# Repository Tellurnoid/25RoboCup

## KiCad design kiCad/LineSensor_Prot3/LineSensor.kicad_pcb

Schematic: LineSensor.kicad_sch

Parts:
A1: Arduino_Nano_v2.x; Arduino_Nano
C2: C; CP_Radial_D5.0mm_P2.50mm
C3: C; C_Disc_D7.5mm_W2.5mm_P5.00mm
C4, C5, C6, C7, C8, C9, C10, C11: C; C_0603_1608Metric
D34, D35, D36, D37, D38, D39, D40, D41, D42, D43, D44, D45, D46, D47, D48, D49: LED; LED_0603_1608Metric
J1: Conn_01x04_Socket; PinSocket_1x04_P2.54mm_Vertical
J2: Conn_01x02_Socket; PinSocket_1x02_P2.54mm_Vertical
Q1, Q2, Q3, Q4, Q5, Q6, Q7, Q8, Q9, Q10, Q11, Q12, Q13, Q14, Q15, Q16: Q_Photo_NPN; NJL7502R
Q17: NMOS; TO-251-3-1EP_Horizontal_TabDown
R1, R2, R3, R4, R5, R6, R7, R8, R9, R10, R11, R12, R13, R14, R15, R16, R17, R18, R19, R20, R21, R22, R23, R24, R25, R26, R27, R28, R29, R30, R31, R32, R33, R34, R35, R36, R37, R38, R39, R40, R41, R42, R43, R44, R45, R46, R55, R56: R; R_0603_1608Metric_Pad0.98x0.95mm_HandSolder
R49, R50, R51, R84, R85: R; R_Axial_DIN0207_L6.3mm_D2.5mm_P7.62mm_Horizontal
RV1, RV2, RV3, RV4: R_Potentiometer_Trim; PinHeader_1x03_P2.54mm_Vertical
SW2: SW_DPST_x2; PinSocket_1x03_P2.54mm_Vertical
U1, U2, U3, U4, U5, U6, U7, U8, U9: LM393; SOIC-8_3.9x4.9mm_P1.27mm

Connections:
unnamed: A1.19 (A0), R25.2, U8.7
unnamed: A1.20 (A1), R26.2, U8.1
unnamed: A1.21 (A2), R27.2, U7.7
unnamed: A1.22 (A3), R28.2, U7.1
unnamed: A1.23 (A4), R32.2, U2.7
unnamed: A1.2 (D0/RX), J1.2
unnamed: A1.1 (D1/TX), R49.2
unnamed: A1.5 (D2), R21.2, U6.7
unnamed: A1.6 (D3), R22.2, U6.1
unnamed: A1.7 (D4), R23.2, U5.7
unnamed: A1.8 (D5), R24.2, U5.1
unnamed: A1.9 (D6), R8.2, U3.1
unnamed: A1.10 (D7), R7.2, U3.7
unnamed: A1.11 (D8), R6.2, U4.1
unnamed: A1.12 (D9), R5.2, U4.7
unnamed: A1.13 (D10), R84.1
unnamed: A1.14 (D11), R29.2, U1.1, U9.1
unnamed: A1.15 (D12), R30.2, U1.7, U9.7
unnamed: A1.16 (D13), R31.2, U2.1
unnamed: D34.1 (K), R55.1
unnamed: D35.1 (K), R56.1
unnamed: D36.1 (K), R40.1
unnamed: D37.1 (K), R41.1
unnamed: D38.1 (K), R42.1
unnamed: D39.1 (K), R43.1
unnamed: D40.1 (K), R44.1
unnamed: D41.1 (K), R45.1
unnamed: D42.1 (K), R46.1
unnamed: D43.1 (K), R39.1
unnamed: D44.1 (K), R38.1
unnamed: D45.1 (K), R37.1
unnamed: D46.1 (K), R36.1
unnamed: D47.1 (K), R35.1
unnamed: D48.1 (K), R34.1
unnamed: D49.1 (K), R33.1
unnamed: J1.1, R49.1, R51.1
unnamed: J2.1, SW2.2 (B)
unnamed: Q1.2 (E), R4.1, U3.2 (-)
unnamed: Q2.2 (E), R3.1, U3.6 (-)
unnamed: Q3.2 (E), R2.1, U4.2 (-)
unnamed: Q4.2 (E), R1.1, U4.6 (-)
unnamed: Q5.2 (E), R13.1, U7.2 (-)
unnamed: Q6.2 (E), R14.1, U7.6 (-)
unnamed: Q7.2 (E), R15.1, U8.2 (-)
unnamed: Q8.2 (E), R16.1, U8.6 (-)
unnamed: Q9.2 (E), R9.1, U6.6 (-)
unnamed: Q10.2 (E), R10.1, U6.2 (-)
unnamed: Q11.2 (E), R11.1, U5.6 (-)
unnamed: Q12.2 (E), R12.1, U5.2 (-)
unnamed: Q13.2 (E), R17.1, U1.2 (-), U9.3 (+)
unnamed: Q14.2 (E), R18.1, U1.6 (-), U9.5 (+)
unnamed: Q15.2 (E), R19.1, U2.2 (-)
unnamed: Q16.2 (E), R20.1, U2.6 (-)
unnamed: Q17.1 (D), R33.2, R34.2, R35.2, R36.2, R37.2, R38.2, R39.2, R40.2, R41.2, R42.2, R43.2, R44.2, R45.2, R46.2, R55.2, R56.2
unnamed: Q17.2 (G), R84.2, R85.2
unnamed: R50.1, R51.2
unnamed: RV4.2, U1.3 (+), U1.5 (+), U2.3 (+), U2.5 (+), U9.2 (-), U9.6 (-)
unnamed: RV1.2, U3.3 (+), U3.5 (+), U4.3 (+), U4.5 (+)
unnamed: RV2.2, U5.3 (+), U5.5 (+), U6.3 (+), U6.5 (+)
unnamed: RV3.2, U7.3 (+), U7.5 (+), U8.3 (+), U8.5 (+)

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
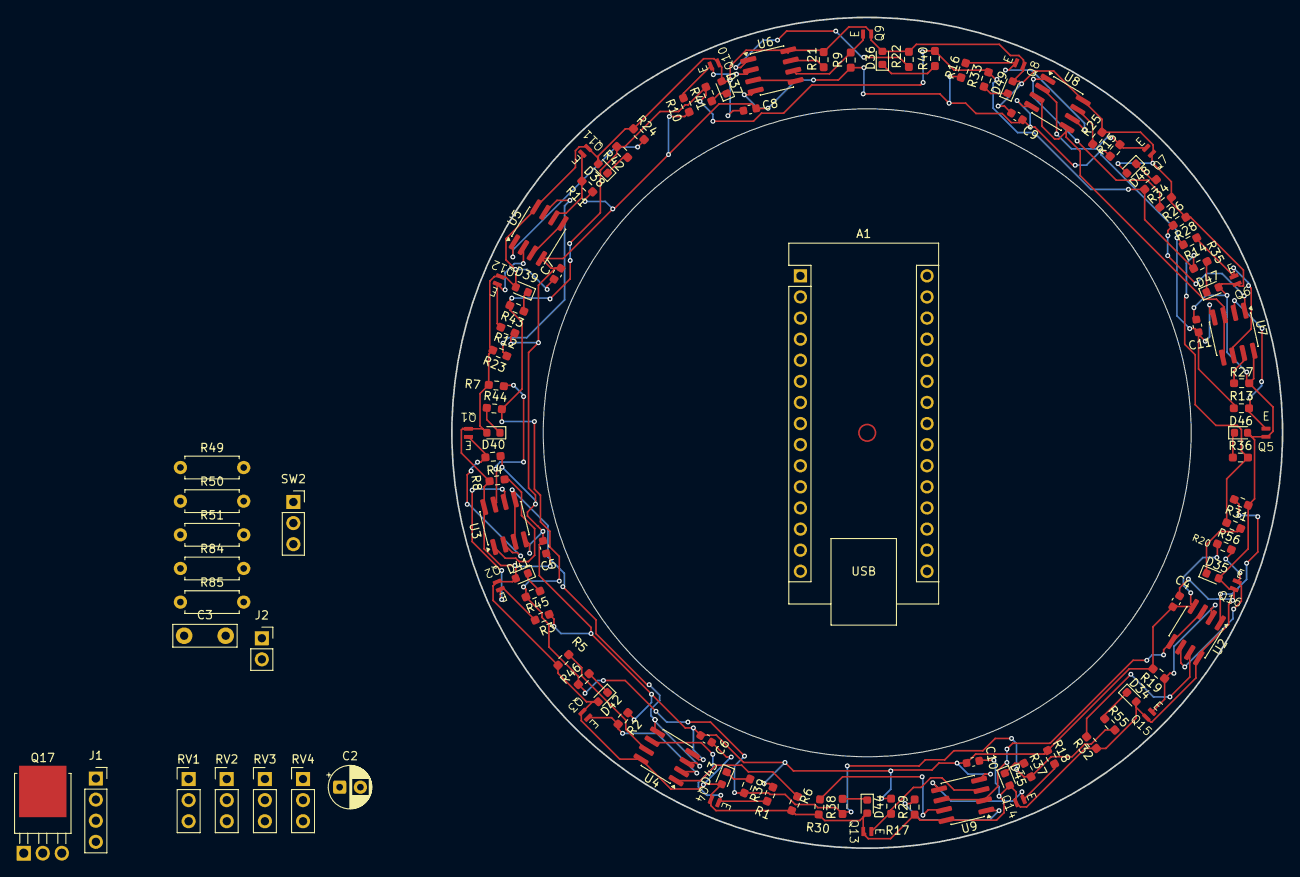
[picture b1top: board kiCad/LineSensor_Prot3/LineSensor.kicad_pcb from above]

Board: 2 copper layers, 100.0 x 100.0 mm, 112 parts (0 on the bottom side), 62 nets.

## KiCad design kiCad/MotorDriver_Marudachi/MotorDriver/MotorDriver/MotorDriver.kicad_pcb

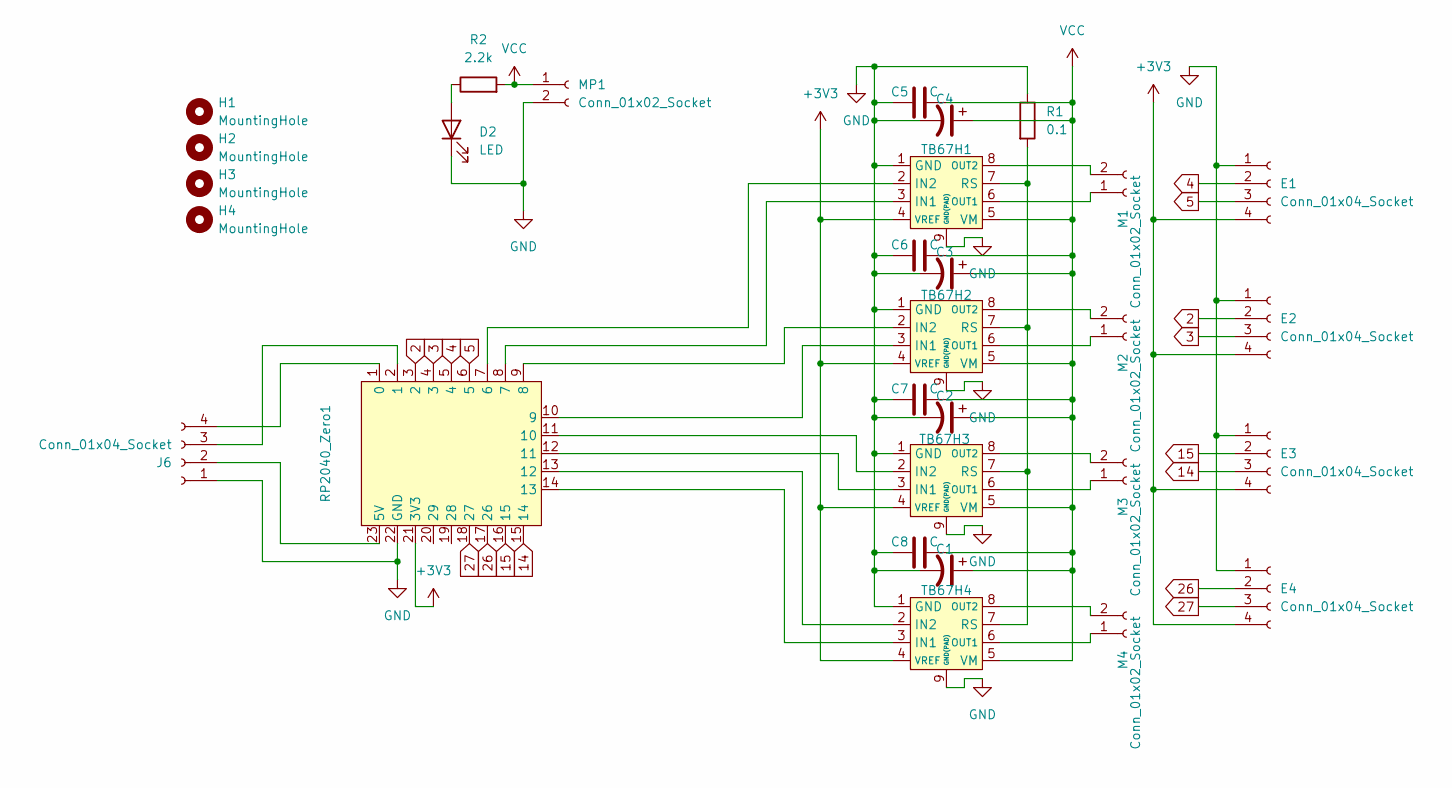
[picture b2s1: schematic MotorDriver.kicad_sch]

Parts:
C1, C2, C3, C4: C_Polarized_US; CP_Radial_D8.0mm_P3.50mm
C5, C6, C7, C8: C; C_0603_1608Metric_Pad1.08x0.95mm_HandSolder
D2: LED; LED_0603_1608Metric_Pad1.05x0.95mm_HandSolder
E1, E2, E3, E4: Conn_01x04_Socket; JST_PH_B4B-PH-K_1x04_P2.00mm_Vertical
H1, H2, H3, H4: MountingHole; MountingHole_3.2mm_M3
J6: Conn_01x04_Socket; JST_XH_B4B-XH-A_1x04_P2.50mm_Vertical
M1, M2, M3, M4: Conn_01x02_Socket; JST_VH_B2P-VH-B_1x02_P3.96mm_Vertical
MP1: Conn_01x02_Socket; AMASS_XT30U-M_1x02_P5.0mm_Vertical
R1: 0.1; R_Axial_DIN0207_L6.3mm_D2.5mm_P7.62mm_Horizontal
R2: 2.2k; R_0603_1608Metric_Pad0.98x0.95mm_HandSolder
RP2040_Zero1: 名称未設定
TB67H1, TB67H2, TB67H3, TB67H4: SOIC-8-1EP_3.9x4.9mm_P1.27mm_EP2.29x3mm_ThermalVias

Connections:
2: E2.2, RP2040_Zero1.3 (2)
3: E2.3, RP2040_Zero1.4 (3)
4: E1.2, RP2040_Zero1.5 (4)
5: E1.3, RP2040_Zero1.6 (5)
14: E3.3, RP2040_Zero1.15 (14)
15: E3.2, RP2040_Zero1.16 (15)
26: E4.2, RP2040_Zero1.17 (26)
27: E4.3, RP2040_Zero1.18 (27)
+3V3: E1.4, E2.4, E3.4, E4.4, RP2040_Zero1.21 (3V3), TB67H1.4 (VREF), TB67H2.4 (VREF), TB67H3.4 (VREF), TB67H4.4 (VREF)
GND: C1.2, C2.2, C3.2, C4.2, C5.1, C6.1, C7.1, C8.1, D2.1 (K), E1.1, E2.1, E3.1, E4.1, J6.1, MP1.2, R1.1, RP2040_Zero1.22 (GND), TB67H1.1 (GND), TB67H1.9 (GND(PAD)), TB67H2.1 (GND), TB67H2.9 (GND(PAD)), TB67H3.1 (GND), TB67H3.9 (GND(PAD)), TB67H4.1 (GND), TB67H4.9 (GND(PAD))
unnamed: D2.2 (A), R2.1
unnamed: J6.2, RP2040_Zero1.23 (5V)
unnamed: J6.3, RP2040_Zero1.2 (1)
unnamed: J6.4, RP2040_Zero1.1 (0)
unnamed: M1.1, TB67H1.6 (OUT1)
unnamed: M1.2, TB67H1.8 (OUT2)
unnamed: M2.1, TB67H2.6 (OUT1)
unnamed: M2.2, TB67H2.8 (OUT2)
unnamed: M3.1, TB67H3.6 (OUT1)
unnamed: M3.2, TB67H3.8 (OUT2)
unnamed: M4.1, TB67H4.6 (OUT1)
unnamed: M4.2, TB67H4.8 (OUT2)
unnamed: RP2040_Zero1.7 (6), TB67H1.2 (IN2)
unnamed: RP2040_Zero1., RP2040_Zero1.8 (7), TB67H1.3 (IN1)
unnamed: RP2040_Zero1.9 (8), TB67H2.2 (IN2)
unnamed: RP2040_Zero1.10 (9), TB67H2.3 (IN1)
unnamed: RP2040_Zero1.11 (10), TB67H3.2 (IN2)
unnamed: RP2040_Zero1.12 (11), TB67H3.3 (IN1)
unnamed: RP2040_Zero1.13 (12), TB67H4.2 (IN2)
unnamed: RP2040_Zero1.14 (13), TB67H4.3 (IN1)
unnamed: R1.2, TB67H1.7 (RS), TB67H2.7 (RS), TB67H3.7 (RS), TB67H4.7 (RS)
VCC: C1.1, C2.1, C3.1, C4.1, C5.2, C6.2, C7.2, C8.2, MP1.1, R2.2, TB67H1.5 (VM), TB67H2.5 (VM), TB67H3.5 (VM), TB67H4.5 (VM)

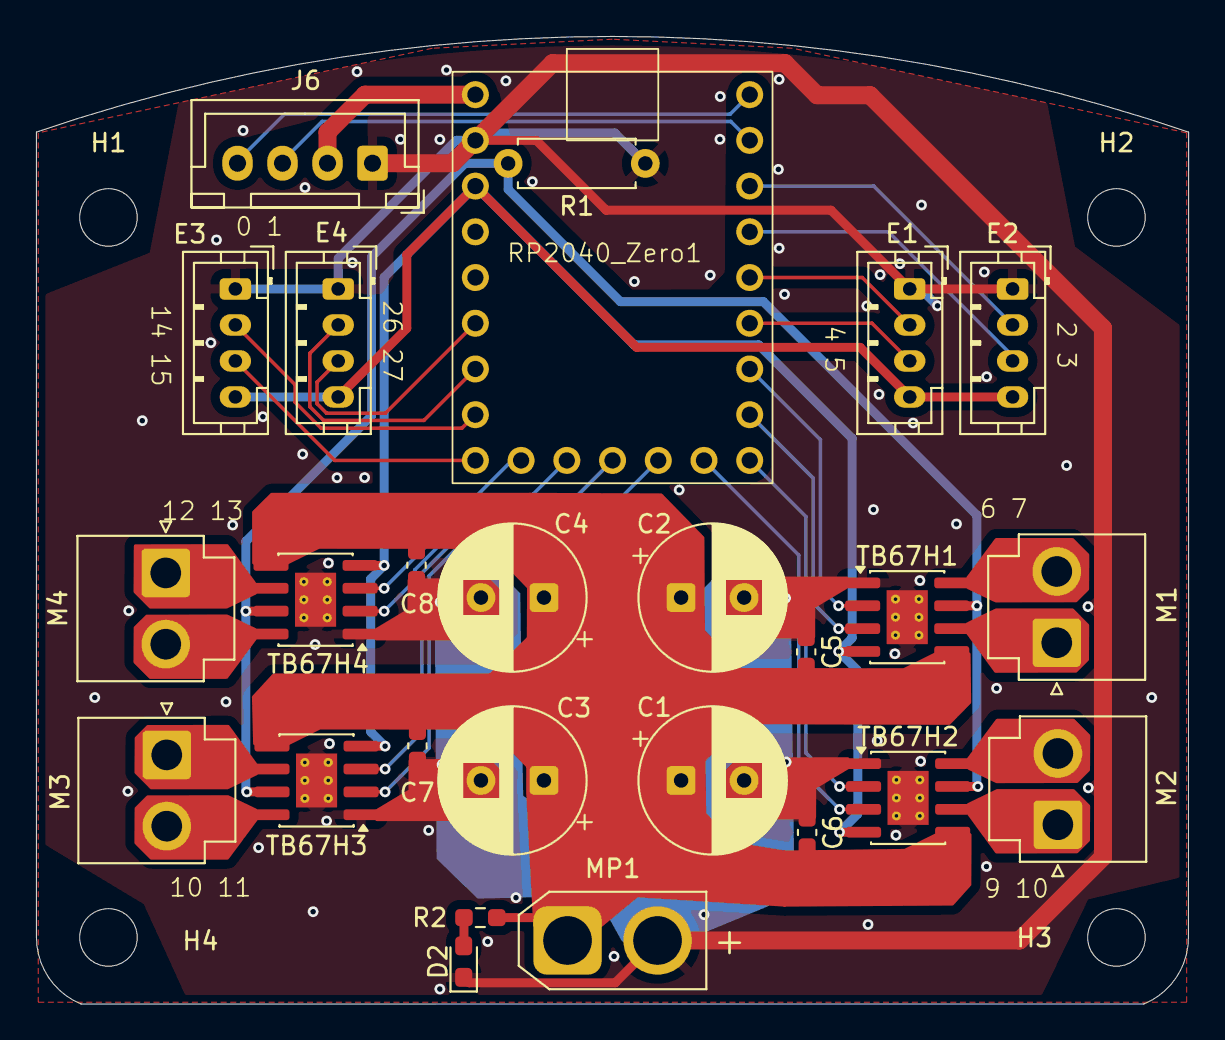
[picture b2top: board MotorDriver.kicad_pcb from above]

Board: 2 copper layers, 64.0 x 53.8 mm, 30 parts (0 on the bottom side), 32 nets.

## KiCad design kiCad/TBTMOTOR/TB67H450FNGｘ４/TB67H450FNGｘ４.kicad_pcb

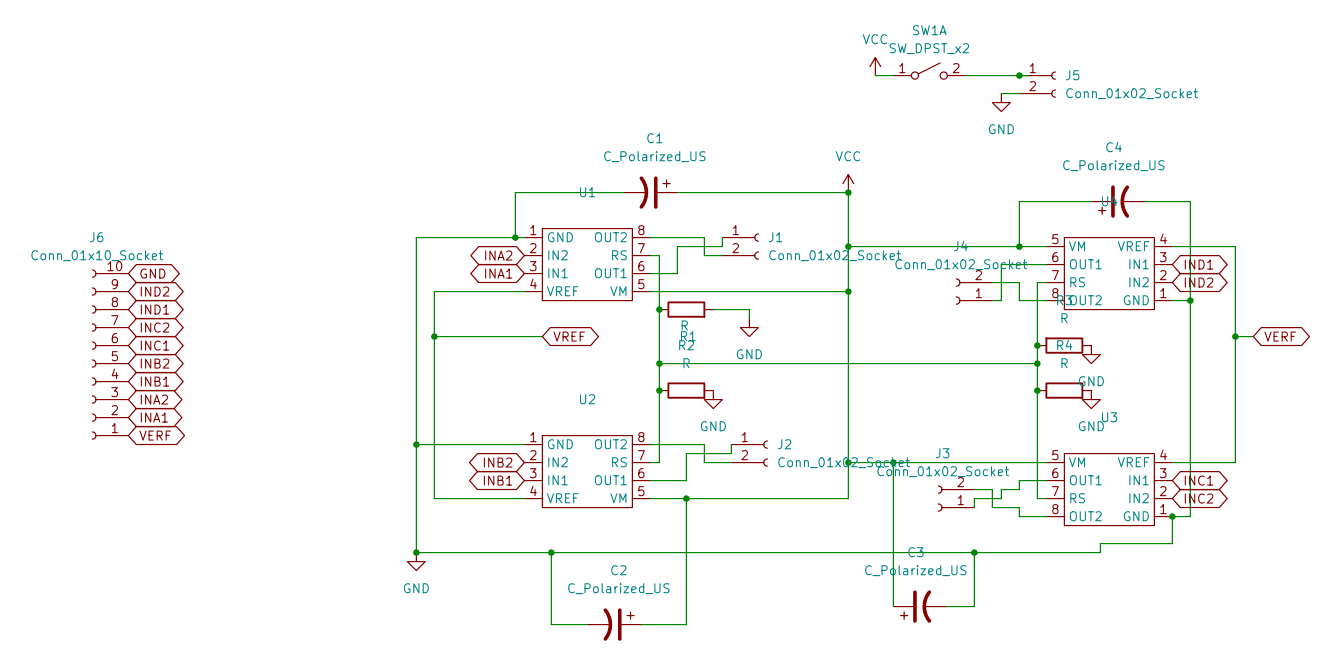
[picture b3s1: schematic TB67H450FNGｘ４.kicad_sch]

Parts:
C1, C2, C3, C4: C_Polarized_US; CP_Radial_D6.3mm_P2.50mm
J1, J2, J3, J4, J5: Conn_01x02_Socket; AMASS_XT30U-M_1x02_P5.0mm_Vertical
J6: Conn_01x10_Socket; JST_XH_B10B-XH-A_1x10_P2.50mm_Vertical
R1, R2, R3, R4: R; R_Axial_DIN0207_L6.3mm_D2.5mm_P10.16mm_Horizontal
SW1: SW_DPST_x2; PinSocket_1x03_P2.54mm_Vertical
U1, U2, U3, U4: Texas_HSOP-8-1EP_3.9x4.9mm_P1.27mm

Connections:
GND: C1.2, C2.2, C3.2, C4.2, J5.2, J6.10, R1.2, R2.2, R3.1, R4.2, U1.1 (GND), U2.1 (GND), U3.1 (GND), U4.1 (GND)
INA1: J6.2, U1.3 (IN1)
INA2: J6.3, U1.2 (IN2)
INB1: J6.4, U2.3 (IN1)
INB2: J6.5, U2.2 (IN2)
INC1: J6.6, U3.3 (IN1)
INC2: J6.7, U3.2 (IN2)
IND1: J6.8, U4.3 (IN1)
IND2: J6.9, U4.2 (IN2)
unnamed: J1.1, U1.6 (OUT1)
unnamed: J1.2, U1.8 (OUT2)
unnamed: J2.1, U2.6 (OUT1)
unnamed: J2.2, U2.8 (OUT2)
unnamed: J3.1, U3.6 (OUT1)
unnamed: J3.2, U3.8 (OUT2)
unnamed: J4.1, U4.6 (OUT1)
unnamed: J4.2, U4.8 (OUT2)
unnamed: J5.1, SW1.2 (B)
unnamed: R1.1, R2.1, R3.2, R4.1, U1.7 (RS), U2.7 (RS), U3.7 (RS), U4.7 (RS)
VCC: C1.1, C2.1, C3.1, C4.1, SW1.1 (A), U1.5 (VM), U2.5 (VM), U3.5 (VM), U4.5 (VM)
VERF: J6.1, U3.4 (VREF), U4.4 (VREF)
VREF: U1.4 (VREF), U2.4 (VREF)

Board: 2 copper layers, 19 parts (0 on the bottom side), 22 nets, no tracks yet.

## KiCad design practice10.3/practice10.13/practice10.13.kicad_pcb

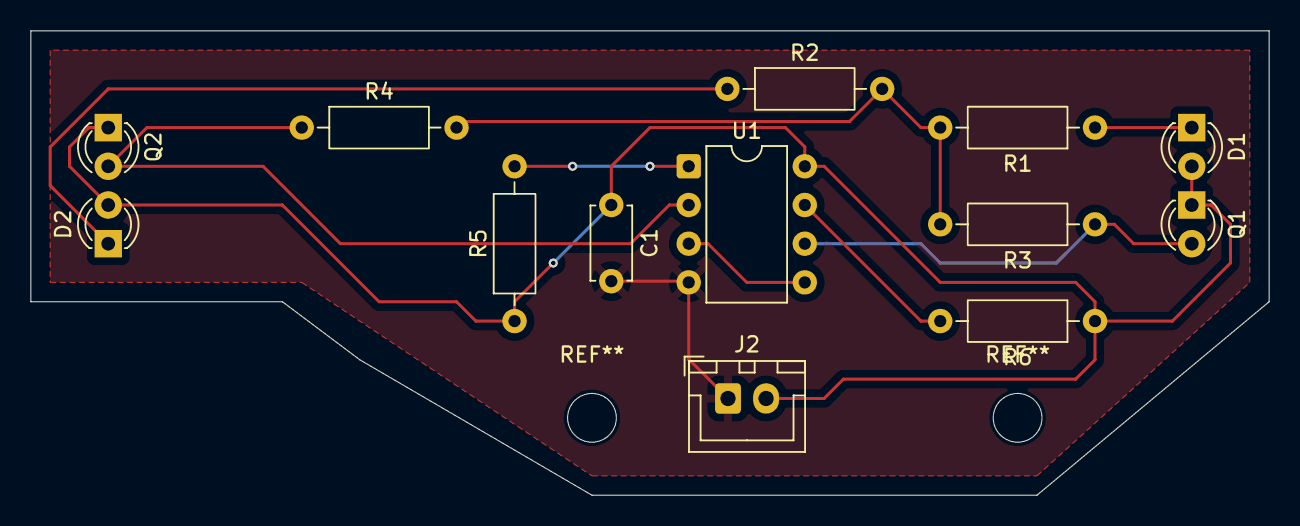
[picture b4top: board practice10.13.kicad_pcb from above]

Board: 2 copper layers, 81.3 x 30.5 mm, 13 parts (0 on the bottom side), 10 nets.

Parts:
C1: C; C_Disc_D4.7mm_W2.5mm_P5.00mm
D1, D2: LED; LED_D3.0mm
J2: Conn_01x05_Socket; JST_XH_B2B-XH-A_1x02_P2.50mm_Vertical
Q1, Q2: Q_Photo_NPN; LED_D3.0mm
R1, R2, R3, R4, R5, R6: R; R_Axial_DIN0207_L6.3mm_D2.5mm_P10.16mm_Horizontal
U1: LM393; DIP-8_W7.62mm

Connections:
GND: C1.2, J2.1, U1.4 (V-)
unnamed: D1.1 (K), R1.1
unnamed: D2.1 (K), R2.1
unnamed: U1.3 (+), U1.5 (+)
unnamed: R6.2, U1.7
unnamed: R5.2, U1.1
unnamed: Q1.2 (E), R3.1, U1.6 (-)
unnamed: Q2.2 (E), R4.1, U1.2 (-)
unnamed: R1.2, R2.2, R3.2, R4.2
VCC: C1.1, D1.2 (A), D2.2 (A), J2.2, Q1.1 (C), Q2.1 (C), R5.1, R6.1, U1.8 (V+)

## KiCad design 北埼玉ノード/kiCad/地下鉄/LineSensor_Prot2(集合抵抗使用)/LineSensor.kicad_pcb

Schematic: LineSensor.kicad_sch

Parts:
A1: Arduino_Nano_v2.x; Arduino_Nano
C2: C; CP_Radial_Tantal_D5.0mm_P5.00mm
C3: C; C_Radial_D6.3mm_H11.0mm_P2.50mm
C4, C5, C6, C7, C8, C9, C10, C11: C; C_0603_1608Metric
D17: D; D_DO-201AD_P12.70mm_Horizontal
D18, D19, D20, D21, D22, D23, D24, D25, D26, D27, D28, D29, D30, D31, D32, D33, D34, D35, D36, D37, D38, D39, D40, D41, D42, D43, D44, D45, D46, D47, D48, D49: LED; LED_0603_1608Metric
J1: Conn_01x04_Socket; PinSocket_1x04_P2.54mm_Vertical
J2: Conn_01x02_Socket; PinSocket_1x02_P2.54mm_Vertical
Q1, Q2, Q3, Q4, Q5, Q6, Q7, Q8, Q9, Q10, Q11, Q12, Q13, Q14, Q15, Q16: Q_Photo_NPN; LED_0603_1608Metric
Q17: NMOS; TO-251-3-1EP_Horizontal_TabDown
R49, R50, R51, R84, R85: R; R_Axial_DIN0207_L6.3mm_D2.5mm_P7.62mm_Horizontal
RN1, RN2, RN3, RN4, RN5, RN6, RN7, RN8, RN9, RN10, RN11, RN12, RN13, RN14, RN15, RN16: R_Network04; R_Array_Convex_4x1206
RV1, RV2, RV3, RV4: R_Potentiometer_Trim; PinHeader_1x03_P2.54mm_Vertical
SW2: SW_DPST_x2; PinSocket_1x03_P2.54mm_Vertical
U1, U2, U3, U4, U5, U6, U7, U8, U9: LM393; SOIC-8_3.9x4.9mm_P1.27mm

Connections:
GND: A1.4 (GND), A1.29 (GND), C2.1, C3.2, C4.2, C5.2, C6.2, C7.2, C8.2, C9.2, C10.2, C11.2, D17.1 (K), J1.3, J2.2, Q17.3 (S), R50.2, R85.1, RN13.1 (common), RN14.1 (common), RN15.1 (common), RN16.1 (common), RV1.3, RV2.3, RV3.3, RV4.3, U2.8 (V+), U3.8 (V+), U4.8 (V+), U5.8 (V+), U6.4 (V-), U7.4 (V-), U8.4 (V-), U9.4 (V-)
unnamed: A1.19 (A0), RN10.5 (R4), U8.7
unnamed: A1.20 (A1), RN10.4 (R3), U8.1
unnamed: A1.21 (A2), RN10.3 (R2), U7.7
unnamed: A1.22 (A3), RN10.2 (R1), U7.1
unnamed: A1.23 (A4), RN9.5 (R4), U2.7
unnamed: A1.2 (D0/RX), J1.2
unnamed: A1.1 (D1/TX), R49.2
unnamed: A1.5 (D2), RN11.2 (R1), U6.7
unnamed: A1.6 (D3), RN11.3 (R2), U6.1
unnamed: A1.7 (D4), RN11.4 (R3), U5.7
unnamed: A1.8 (D5), RN11.5 (R4), U5.1
unnamed: A1.9 (D6), RN12.2 (R1), U3.1
unnamed: A1.10 (D7), RN12.3 (R2), U3.7
unnamed: A1.11 (D8), RN12.4 (R3), U4.1
unnamed: A1.12 (D9), RN12.5 (R4), U4.7
unnamed: A1.13 (D10), R84.1
unnamed: A1.14 (D11), RN9.2 (R1), U1.1
unnamed: A1.15 (D12), RN9.3 (R2), U1.7
unnamed: A1.16 (D13), RN9.4 (R3), U2.1
unnamed: D18.1 (K), RN1.5 (R4)
unnamed: D19.1 (K), RN1.4 (R3)
unnamed: D20.1 (K), RN1.3 (R2)
unnamed: D21.1 (K), RN1.2 (R1)
unnamed: D22.1 (K), RN2.5 (R4)
unnamed: D23.1 (K), RN2.4 (R3)
unnamed: D24.1 (K), RN2.3 (R2)
unnamed: D25.1 (K), RN2.2 (R1)
unnamed: D26.1 (K), RN3.5 (R4)
unnamed: D27.1 (K), RN3.4 (R3)
unnamed: D28.1 (K), RN3.3 (R2)
unnamed: D29.1 (K), RN3.2 (R1)
unnamed: D30.1 (K), RN4.5 (R4)
unnamed: D31.1 (K), RN4.4 (R3)
unnamed: D32.1 (K), RN4.3 (R2)
unnamed: D33.1 (K), RN4.2 (R1)
unnamed: D34.1 (K), RN5.5 (R4)
unnamed: D35.1 (K), RN5.4 (R3)
unnamed: D36.1 (K), RN5.3 (R2)
unnamed: D37.1 (K), RN5.2 (R1)
unnamed: D38.1 (K), RN6.5 (R4)
unnamed: D39.1 (K), RN6.4 (R3)
unnamed: D40.1 (K), RN6.3 (R2)
unnamed: D41.1 (K), RN6.2 (R1)
unnamed: D42.1 (K), RN7.5 (R4)
unnamed: D43.1 (K), RN7.4 (R3)
unnamed: D44.1 (K), RN7.3 (R2)
unnamed: D45.1 (K), RN7.2 (R1)
unnamed: D46.1 (K), RN8.5 (R4)
unnamed: D47.1 (K), RN8.4 (R3)
unnamed: D48.1 (K), RN8.3 (R2)
unnamed: D49.1 (K), RN8.2 (R1)
unnamed: J1.1, R49.1, R51.1
unnamed: J2.1, SW2.2 (B)
unnamed: Q1.2 (E), RN15.5 (R4), U3.3 (+)
unnamed: Q2.2 (E), RN15.4 (R3), U3.5 (+)
unnamed: Q3.2 (E), RN15.3 (R2), U4.3 (+)
unnamed: Q4.2 (E), RN15.2 (R1), U4.5 (+)
unnamed: Q5.2 (E), RN13.2 (R1), U8.6 (-)
unnamed: Q6.2 (E), RN13.3 (R2), U8.2 (-)
unnamed: Q7.2 (E), RN13.4 (R3), U7.6 (-)
unnamed: Q8.2 (E), RN13.5 (R4), U7.2 (-)
unnamed: Q9.2 (E), RN16.5 (R4), U6.5 (+)
unnamed: Q10.2 (E), RN16.4 (R3), U6.3 (+)
unnamed: Q11.2 (E), RN16.3 (R2), U5.5 (+)
unnamed: Q12.2 (E), RN16.2 (R1), U5.3 (+)
unnamed: Q13.2 (E), RN14.5 (R4), U1.3 (+)
unnamed: Q14.2 (E), RN14.4 (R3), U1.5 (+)
unnamed: Q15.2 (E), RN14.3 (R2), U2.3 (+)
unnamed: Q16.2 (E), RN14.2 (R1), U2.5 (+)
unnamed: Q17.1 (D), RN1.1 (common), RN2.1 (common), RN3.1 (common), RN4.1 (common), RN5.1 (common), RN6.1 (common), RN7.1 (common), RN8.1 (common)
unnamed: Q17.2 (G), R84.2, R85.2
unnamed: R50.1, R51.2
unnamed: RV4.2, U1.2 (-), U1.6 (-), U2.2 (-), U2.6 (-)
unnamed: RV1.2, U3.2 (-), U3.6 (-), U4.2 (-), U4.6 (-)
unnamed: RV2.2, U5.2 (-), U5.6 (-), U6.2 (-), U6.6 (-)
unnamed: RV3.2, U7.3 (+), U7.5 (+), U8.3 (+), U8.5 (+)
VCC: A1.27 (+5V), C2.2, C3.1, C4.1, C5.1, C6.1, C7.1, C8.1, C9.1, C10.1, C11.1, D17.2 (A), D18.2 (A), D19.2 (A), D20.2 (A), D21.2 (A), D22.2 (A), D23.2 (A), D24.2 (A), D25.2 (A), D26.2 (A), D27.2 (A), D28.2 (A), D29.2 (A), D30.2 (A), D31.2 (A), D32.2 (A), D33.2 (A), D34.2 (A), D35.2 (A), D36.2 (A), D37.2 (A), D38.2 (A), D39.2 (A), D40.2 (A), D41.2 (A), D42.2 (A), D43.2 (A), D44.2 (A), D45.2 (A), D46.2 (A), D47.2 (A), D48.2 (A), D49.2 (A), J1.4, Q1.1 (C), Q2.1 (C), Q3.1 (C), Q4.1 (C), Q5.1 (C), Q6.1 (C), Q7.1 (C), Q8.1 (C), Q9.1 (C), Q10.1 (C), Q11.1 (C), Q12.1 (C), Q13.1 (C), Q14.1 (C), Q15.1 (C), Q16.1 (C), RN9.1 (common), RN10.1 (common), RN11.1 (common), RN12.1 (common), RV1.1, RV2.1, RV3.1, RV4.1, SW2.1 (A), U2.4 (V-), U3.4 (V-), U4.4 (V-), U5.4 (V-), U6.8 (V+), U7.8 (V+), U8.8 (V+), U9.8 (V+)

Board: 2 copper layers, 98 parts (0 on the bottom side), 78 nets, no tracks yet.
